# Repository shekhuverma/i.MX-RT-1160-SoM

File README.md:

You can read the full blog post [here](https://shekharverma.com/posts/imxrt_som/)!

**The SoM Features**
* i.MX RT 1160 MCU (MIMXRT1166DVM6A)
* 128 Mb SD RAM
* 128 Mb QSPI Flash
* 4 Gb eMMC
* 10/100 Mbps RMII Ethernet PHY
* 2 Lane MIPI-DSI
* 2 Lane MIPI-CSI
* 2 X USB 2.0
* 2 X I2C
* UART to USB Convertor
* Multiple GPIOs
* 2 X 48 Pin Board-to-Board Connector

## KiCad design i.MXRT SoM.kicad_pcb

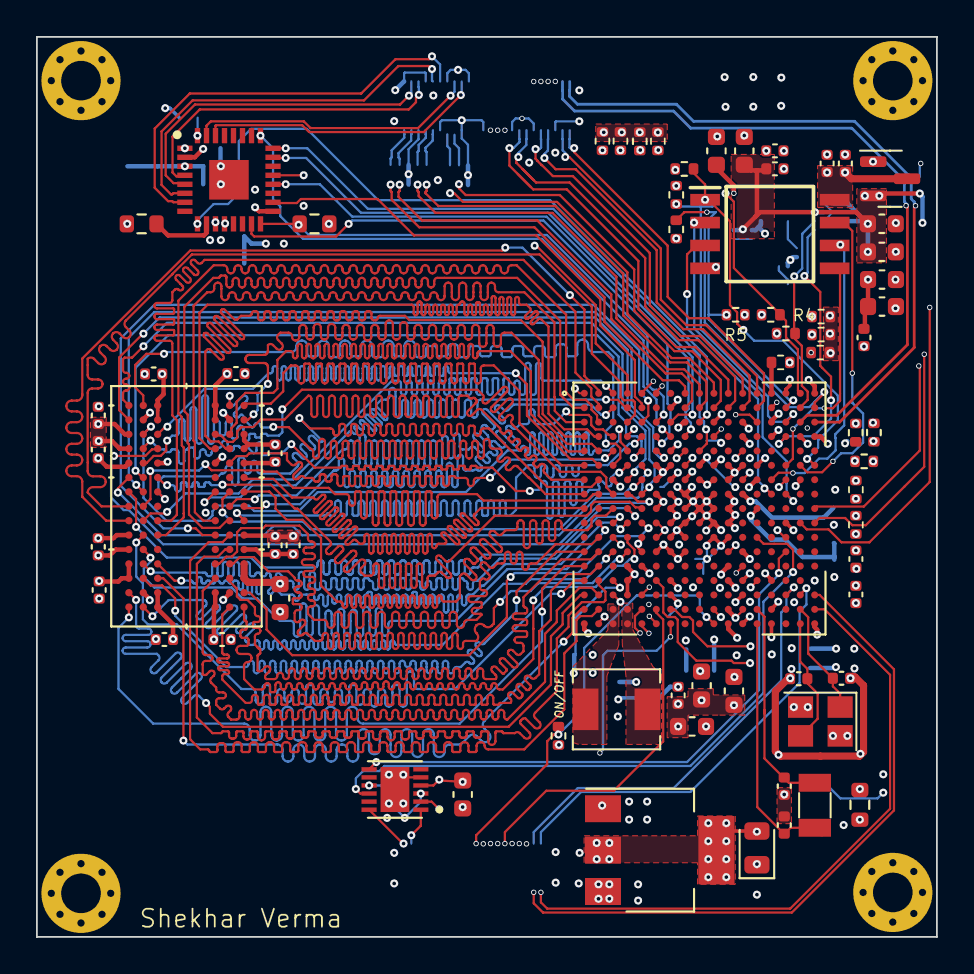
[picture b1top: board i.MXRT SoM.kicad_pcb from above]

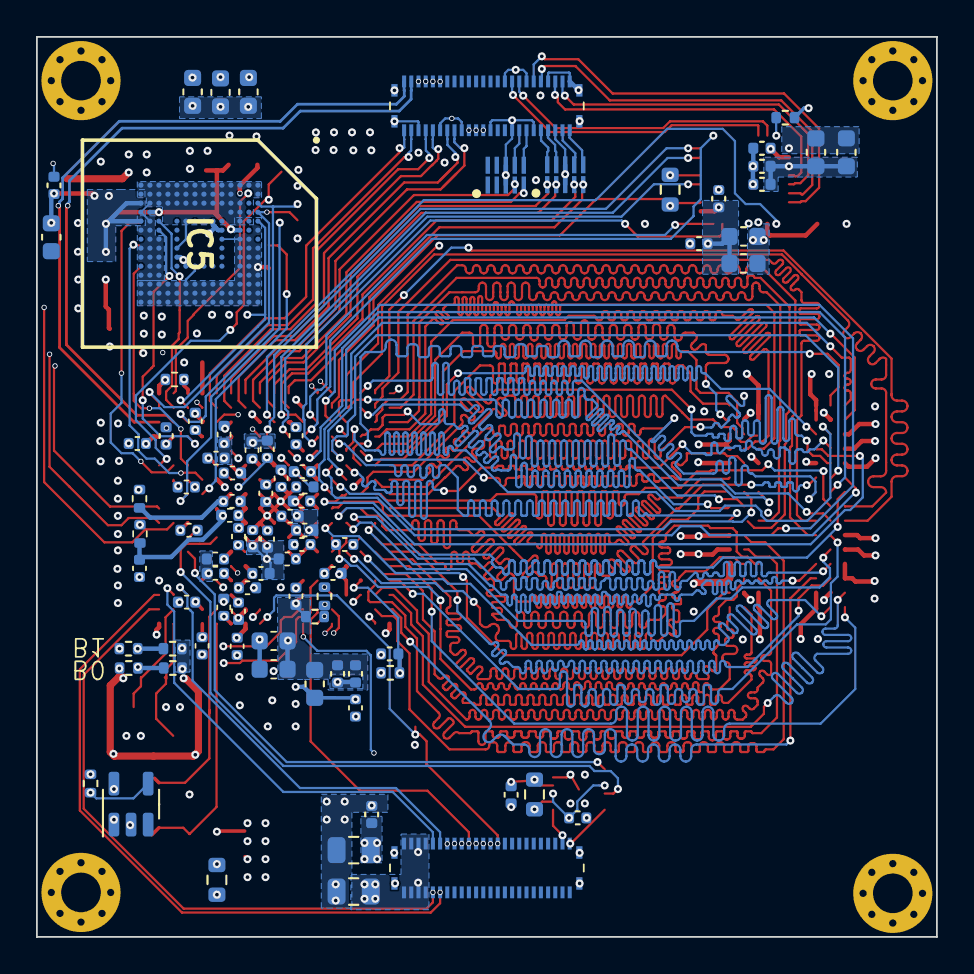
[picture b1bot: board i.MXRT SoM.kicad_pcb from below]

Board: 6 copper layers, 50.0 x 50.0 mm, 157 parts (85 on the bottom side), 170 nets.

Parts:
C1, C43, C49, C50, C58: 22uF; C_0603_1608Metric
C2, C8, C9, C10, C11, C21, C31, C35, C45, C57: 4.7uF; C_0402_1005Metric
C3, C15, C16, C26, C37, C41, C46, C48, C51, C53, C59, C60, C61, C62, C63, C64, C65, C66, C67, C68, C76, C89, C96: 0.1uF; C_0402_1005Metric
C4, C5, C6, C14, C20, C25, C28, C32, C36, C55: 1uF; C_0402_1005Metric
C7, C17: 0.22uF; C_0402_1005Metric
C12, C13, C18, C19, C22, C23, C24, C27, C29, C30, C33, C34, C40, C44, C69, C92, C99: 2.2uF; C_0402_1005Metric
C38, C39, C87, C88: 4.7pF; C_0402_1005Metric
C42, C47, C78, C82: 10uF; C_0603_1608Metric
C52, C72, C80, C83, C85: 100nF; C_0402_1005Metric
C54, C73, C81, C86, C98: 1uF; C_0603_1608Metric
C56: 2nF; C_0402_1005Metric
C70, C71: 10uF; C_0805_2012Metric
C74, C75: 2.2uF; C_0603_1608Metric
C77, C79: 10nF; C_0402_1005Metric
C84: 4.7uF; C_0603_1608Metric
C90, C91, C93, C94, C95: 0.1uF; C_0603_1608Metric
D1: Green LED; LED_0805_2012Metric
FB1, FB2, FB3, FB4: 120Ohm@100Mhz; R_0402_1005Metric
H1, H2, H3, H4: MountingHole_Pad; MountingHole_2.2mm_M2_Pad_Via
IC1, IC2: ECMF04-4HSM10
IC3: DP83826ERHBR; QFN50P500X500X100-33N-D
IC5: THGBMTG5D1LBAIL; BGA153C50P14X14_1150X1300X80
IC6: W25Q16JVSSIQ; SOIC127P790X216-8N
J1, J2: DF40GB-48DP-0.4V_58_; DF40GB48DP04V58
L1: 4.7uH; AMDLA4020Q-4R7MT
R1: 30K; R_0402_1005Metric
R2, R3, R4, R5, R7, R8, R32: 10K; R_0402_1005Metric
R6, R11: 4.7K; R_0402_1005Metric
R9, R12, R25, R26: DNP; R_0402_1005Metric
R10, R13, R14, R15, R16, R17, R18, R19, R20, R21, R22, R23, R24: 100K; R_0402_1005Metric
R27: 100; R_0603_1608Metric
R28, R41: 10K; R_0603_1608Metric
R29: 6.49K 1%; R_0603_1608Metric
R30, R31: 2.49K 1%; R_0603_1608Metric
R36: 0; R_0402_1005Metric
U1: MIMXRT1166DVM6A
U3: AS4C4M32S-6BIN
U4: LD1117S33TR_SOT223; SOT-223-3_TabPin2
U5: RP300N27AA; SOT-23-5
U6: FT234XD-R; SON45P300X300X80-13N
U7: MCP1700T-1802E/TT; SOT-23
Y1: Crystal_GND24; Crystal_SMD_SeikoEpson_FA238-4Pin_3.2x2.5mm
Y3: 32.768Khz; Crystal_SMD_3215-2Pin_3.2x1.5mm

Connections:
5V: C70.1, J2.21, J2.22, J2.23, J2.24, J2.45, J2.46, J2.47, J2.48, U4.3 (VI)
/MCU_POWER/VDD_SNVS_DIG: C17.1, U1.T14 (VDD_SNVS_DIG)
A0: U1.A3 (GPIO_EMC_B1_09), U3.G8 (A0)
A1: U1.A2 (GPIO_EMC_B1_10), U3.G9 (A1)
A2: U1.C2 (GPIO_EMC_B1_11), U3.F7 (A2)
A3: U1.C5 (GPIO_EMC_B1_12), U3.F3 (A3)
A4: U1.D5 (GPIO_EMC_B1_13), U3.G1 (A4)
A5: U1.B1 (GPIO_EMC_B1_14), U3.G2 (A5)
A6: U1.C1 (GPIO_EMC_B1_15), U3.G3 (A6)
A7: U1.D3 (GPIO_EMC_B1_16), U3.H1 (A7)
A8: U1.B3 (GPIO_EMC_B1_17), U3.H2 (A8)
A9: U1.B4 (GPIO_EMC_B1_18), U3.J3 (A9)
A10: U1.B2 (GPIO_EMC_B1_23), U3.G7 (A10)
A11: U1.C4 (GPIO_EMC_B1_19), U3.H9 (A11)
BA0: U1.G2 (GPIO_EMC_B1_21), U3.J7 (BA0)
BA1: U1.H2 (GPIO_EMC_B1_22), U3.H8 (BA1)
CSI_CK_N: J1.5, U1.A12 (MIPI_CSI_CKN)
CSI_CK_P: J1.4, U1.B12 (MIPI_CSI_CKP)
CSI_D0_N: J1.8, U1.A11 (MIPI_CSI_DN0)
CSI_D0_P: J1.7, U1.B11 (MIPI_CSI_DP0)
CSI_D1_N: J1.2, U1.A13 (MIPI_CSI_DN1)
CSI_D1_P: J1.1, U1.B13 (MIPI_CSI_DP1)
DCDC_1V8: C20.1, C26.1, C33.1, C37.1, C40.1, C42.1, C43.1, C46.1, FB1.2, FB3.2, U1.G16 (ADC_VREFH), U1.K15 (VDDA_ADC_1P8), U1.M6 (DCDC_ANA_SENSE), U1.M7 (DCDC_ANA), U1.M8 (DCDC_ANA), U1.M11 (VDDA_1P8_IN)
DCDC_IN: C4.1, C10.1, C11.1, C12.1, C13.1, C18.1, C21.1, C22.1, C23.1, C24.1, C27.1, C30.1, C31.1, C45.1, C48.1, C50.1, C52.1, C53.1, C54.1, C55.1, C57.1, C58.1, C59.1, C60.1, C61.1, C62.1, C63.1, C64.1, C65.1, C66.1, C67.1, C68.1, C71.1, C72.1, C74.1, C75.1, C76.2, C77.1, C78.1, C79.2, C80.2, C81.2, C82.2, C83.1, C84.1, C86.2, C89.2, C90.2, C91.2, D1.2 (A), FB2.2, FB4.2, IC3.3 (VDDA3V3), IC3.17 (VDDIO), IC5.E6 (VCC_1), IC5.F5 (VCC_2), IC5.J10 (VCC_3), IC5.K9 (VCC_4), IC6.8 (VCC), R1.2, R2.2, R3.2, R4.2, R5.2, R7.2, R8.2, R9.2, R11.2, R26.1, R28.1, R31.1, R32.1, R41.2, U1.D12 (NVCC_DISP1), U1.D14 (NVCC_SD1), U1.E7 (NVCC_DISP2), U1.F6 (NVCC_EMC1), U1.F7 (NVCC_EMC1), U1.G6 (NVCC_EMC1), U1.G13 (NVCC_SD2), U1.H6 (NVCC_EMC2), U1.J6 (NVCC_EMC2), U1.L5 (DCDC_IN_Q), U1.M5 (DCDC_IN), U1.M12 (NVCC_GPIO), U1.N5 (DCDC_IN), U1.P7 (NVCC_LPSR), U1.R12 (VDD_LPSR_IN), U1.U12 (VDD_SNVS_IN), U3.A7 (VDD), U3.B2 (VDDQ), U3.B7 (VDDQ), U3.C9 (VDDQ), U3.D9 (VDDQ), U3.E1 (VDDQ), U3.F9 (VDD), U3.L1 (VDDQ), U3.L7 (VDD), U3.M9 (VDDQ), U3.N9 (VDDQ), U3.P2 (VDDQ), U3.P7 (VDDQ), U3.R7 (VDD), U4.2 (VO), U5.5 (VDD), U6.4 (VCC), U7.3 (VI)
DCDC_LN: L1.1, U1.T4 (DCDC_LN), U1.U4 (DCDC_LN)
DCDC_LP: L1.2, U1.T3 (DCDC_LP), U1.U3 (DCDC_LP)
DQ0: U1.F3 (GPIO_EMC_B1_00), U3.R8 (DQ0)
DQ1: U1.F2 (GPIO_EMC_B1_01), U3.N7 (DQ1)
DQ2: U1.G4 (GPIO_EMC_B1_02), U3.R9 (DQ2)
DQ3: U1.E4 (GPIO_EMC_B1_03), U3.N8 (DQ3)
DQ4: U1.H5 (GPIO_EMC_B1_04), U3.P9 (DQ4)
DQ5: U1.F4 (GPIO_EMC_B1_05), U3.M8 (DQ5)
DQ6: U1.H4 (GPIO_EMC_B1_06), U3.M7 (DQ6)
DQ7: U1.H3 (GPIO_EMC_B1_07), U3.L8 (DQ7)
DQ8: U1.E3 (GPIO_EMC_B1_30), U3.L2 (DQ8)
DQ9: U1.D2 (GPIO_EMC_B1_31), U3.M3 (DQ9)
DQ10: U1.D1 (GPIO_EMC_B1_32), U3.M2 (DQ10)
DQ11: U1.E2 (GPIO_EMC_B1_33), U3.P1 (DQ11)
DQ12: U1.E1 (GPIO_EMC_B1_34), U3.N2 (DQ12)
DQ13: U1.F1 (GPIO_EMC_B1_35), U3.R1 (DQ13)
DQ14: U1.G1 (GPIO_EMC_B1_36), U3.N3 (DQ14)
DQ15: U1.H1 (GPIO_EMC_B1_37), U3.R2 (DQ15)
DQ16: U1.K2 (GPIO_EMC_B2_00), U3.E8 (DQ16)
DQ17: U1.K4 (GPIO_EMC_B2_01), U3.D7 (DQ17)
DQ18: U1.K3 (GPIO_EMC_B2_02), U3.D8 (DQ18)
DQ19: U1.R1 (GPIO_EMC_B2_03), U3.B9 (DQ19)
DQ20: U1.M1 (GPIO_EMC_B2_04), U3.C8 (DQ20)
DQ21: U1.N1 (GPIO_EMC_B2_05), U3.A9 (DQ21)
DQ22: U1.T1 (GPIO_EMC_B2_06), U3.C7 (DQ22)
DQ23: U1.M3 (GPIO_EMC_B2_07), U3.A8 (DQ23)
DQ24: U1.N2 (GPIO_EMC_B2_09), U3.A2 (DQ24)
DQ25: U1.R2 (GPIO_EMC_B2_10), U3.C3 (DQ25)
DQ26: U1.L4 (GPIO_EMC_B2_11), U3.A1 (DQ26)
DQ27: U1.M2 (GPIO_EMC_B2_12), U3.C2 (DQ27)
DQ28: U1.K5 (GPIO_EMC_B2_13), U3.B1 (DQ28)
DQ29: U1.M4 (GPIO_EMC_B2_14), U3.D2 (DQ29)
DQ30: U1.L2 (GPIO_EMC_B2_15), U3.D3 (DQ30)
DQ31: U1.P2 (GPIO_EMC_B2_16), U3.E2 (DQ31)
DQM0: U1.F5 (GPIO_EMC_B1_08), U3.K9 (DQM0)
DQM1: U1.J1 (GPIO_EMC_B1_38), U3.K1 (DQM1)
DQM2: U1.P1 (GPIO_EMC_B2_08), U3.F8 (DQM2)
DQM3: U1.T2 (GPIO_EMC_B2_17), U3.F2 (DQM3)
DSI_CK_MCU_N: IC1.2 (D1-_1), U1.A9 (MIPI_DSI_CKN)
DSI_CK_MCU_P: IC1.1 (D1+_1), U1.B9 (MIPI_DSI_CKP)
DSI_CK_N: IC1.9 (D1-_2), J1.21
DSI_CK_P: IC1.10 (D1+_2), J1.20
DSI_D0_MCU_N: IC1.5 (D2-_1), U1.A8 (MIPI_DSI_DN0)
DSI_D0_MCU_P: IC1.4 (D2+_1), U1.B8 (MIPI_DSI_DP0)
DSI_D0_N: IC1.6 (D2-_2), J1.24
DSI_D0_P: IC1.7 (D2+_2), J1.23
DSI_D1_MCU_N: IC2.5 (D2-_1), U1.A10 (MIPI_DSI_DN1)
DSI_D1_MCU_P: IC2.4 (D2+_1), U1.B10 (MIPI_DSI_DP1)
DSI_D1_N: IC2.6 (D2-_2), J1.18
DSI_D1_P: IC2.7 (D2+_2), J1.17
EMMC_CLK: IC5.M6 (CLK), U1.D15 (GPIO_SD_B1_01)
EMMC_CMD: IC5.M5 (CMD), R2.1, U1.B16 (GPIO_SD_B1_00)
EMMC_D0: IC5.A3 (DAT0), R8.1, U1.C15 (GPIO_SD_B1_02)
EMMC_D1: IC5.A4 (DAT1), R7.1, U1.B17 (GPIO_SD_B1_03)
EMMC_D2: IC5.A5 (DAT2), R5.1, U1.B15 (GPIO_SD_B1_04)
EMMC_D3: IC5.B2 (DAT3), R4.1, U1.A16 (GPIO_SD_B1_05)
ENET_CRS_DV: IC3.18 (RX_DV/CRS_DV/STRAP10), U1.B5 (GPIO_DISP_B2_08)
ENET_INT: IC3.21 (PWRDN/INT), R31.2, U1.P17 (GPIO_AD_12)
ENET_LED0: IC3.30 (LED0/STRAP2), J1.40
ENET_LED1: IC3.31 (CLKOUT/LED1/STRAP1), J1.41
ENET_MDC: IC3.12 (MDC), U1.U2 (GPIO_EMC_B2_19)
ENET_MDIO: IC3.11 (MDIO), U1.R3 (GPIO_EMC_B2_20)
ENET_RST: IC3.32 (RST_N), R36.2
ENET_RX_D0: IC3.16 (STRAP0/RX_D0), R30.2, U1.C6 (GPIO_DISP_B2_06)
ENET_RX_D1: IC3.15 (STRAP9/RX_D1), U1.D6 (GPIO_DISP_B2_07)
ENET_RX_ER: IC3.20 (RX_ER/STRAP6), U1.D8 (GPIO_DISP_B2_09)
ENET_TX_CLK: IC3.9 (XI/50MHZIN), R20.2, U1.C9 (GPIO_DISP_B2_05)
ENET_TX_D0: IC3.24 (TX_D0), R23.2, U1.E9 (GPIO_DISP_B2_02)
ENET_TX_D1: IC3.25 (TX_D1), R24.2, U1.D7 (GPIO_DISP_B2_03)
ENET_TX_EN: IC3.23 (TX_EN), R19.2, U1.C7 (GPIO_DISP_B2_04)
GND: C1.2, C2.2, C3.2, C4.2, C5.2, C6.2, C7.2, C8.2, C9.2, C10.2, C11.2, C12.2, C13.2, C14.2, C15.2, C16.2, C17.2, C18.2, C19.2, C20.2, C21.2, C22.2, C23.2, C24.2, C25.2, C26.2, C27.2, C28.2, C29.2, C30.2, C31.2, C32.2, C33.2, C34.1, C35.1, C36.2, C37.2, C38.1, C39.2, C40.2, C41.2, C42.2, C43.2, C44.2, C45.2, C46.2, C47.2, C48.2, C49.2, C50.2, C51.2, C52.2, C53.2, C54.2, C55.2, C56.1, C57.2, C58.2, C59.2, C60.2, C61.2, C62.2, C63.2, C64.2, C65.2, C66.2, C67.2, C68.2, C69.2, C70.2, C71.2, C72.2, C73.2, C74.2, C75.2, C76.1, C77.2, C78.2, C79.1, C80.1, C81.1, C82.1, C83.2, C84.2, C85.2, C86.1, C87.1, C88.2, C89.1, C90.1, C91.1, C92.2, C93.1, C94.1, C95.1, C96.1, C98.1, C99.2, H1.1, H2.1, H3.1, H4.1, IC1.3 (GND_1), IC1.8 (GND_2), IC2.3 (GND_1), IC2.8 (GND_2), IC3.1 (MODESELECT), IC3.33 (EP), IC5.A1 (NC), IC5.A2 (NC), IC5.A6 (VSS_1), IC5.A8 (NC), IC5.A9 (NC), IC5.A10 (NC), IC5.A11 (NC), IC5.A12 (NC), IC5.A13 (NC), IC5.A14 (NC), IC5.B1 (NC), IC5.B7 (NC), IC5.B8 (NC), IC5.B9 (NC), IC5.B10 (NC), IC5.B11 (NC), IC5.B12 (NC), IC5.B13 (NC), IC5.B14 (NC), IC5.C1 (NC), IC5.C3 (NC), IC5.C4 (VSSQ_1), IC5.C5 (NC), IC5.C7 (NC), IC5.C8 (NC), IC5.C9 (NC), IC5.C10 (NC), IC5.C11 (NC), IC5.C12 (NC), IC5.C13 (NC), IC5.C14 (NC), IC5.D1 (NC), IC5.D2 (NC), IC5.D3 (NC), IC5.D4 (NC), IC5.D12 (NC), IC5.D13 (NC), IC5.D14 (NC), IC5.E1 (NC), IC5.E2 (NC), IC5.E3 (NC), IC5.E7 (VSS_2), IC5.E12 (NC), IC5.E13 (NC), IC5.E14 (NC), IC5.F1 (NC), IC5.F2 (NC), IC5.F3 (NC), IC5.F12 (NC), IC5.F13 (NC), IC5.F14 (NC), IC5.G1 (NC), IC5.G2 (NC), IC5.G3 (NC), IC5.G5 (VSS_3), IC5.G12 (NC), IC5.G13 (NC), IC5.G14 (NC), IC5.H1 (NC), IC5.H2 (NC), IC5.H3 (NC), IC5.H10 (VSS_4), IC5.H12 (NC), IC5.H13 (NC), IC5.H14 (NC), IC5.J1 (NC), IC5.J2 (NC), IC5.J3 (NC), IC5.J5 (VSS_5), IC5.J12 (NC), IC5.J13 (NC), IC5.J14 (NC), IC5.K1 (NC), IC5.K2 (NC), IC5.K3 (NC), IC5.K8 (VSS_6), IC5.K12 (NC), IC5.K13 (NC), IC5.K14 (NC), IC5.L1 (NC), IC5.L2 (NC), IC5.L3 (NC), IC5.L12 (NC), IC5.L13 (NC), IC5.L14 (NC), IC5.M1 (NC), IC5.M2 (NC), IC5.M3 (NC), IC5.M7 (NC), IC5.M8 (NC), IC5.M9 (NC), IC5.M10 (NC), IC5.M11 (NC), IC5.M12 (NC), IC5.M13 (NC), IC5.M14 (NC), IC5.N1 (NC), IC5.N2 (VSSQ_2), IC5.N3 (NC), IC5.N5 (VSSQ_3), IC5.N6 (NC), IC5.N7 (NC), IC5.N8 (NC), IC5.N9 (NC), IC5.N10 (NC), IC5.N11 (NC), IC5.N12 (NC), IC5.N13 (NC), IC5.N14 (NC), IC5.P1 (NC), IC5.P2 (NC), IC5.P4 (VSSQ_4), IC5.P6 (VSSQ_5), IC5.P8 (NC), IC5.P9 (NC), IC5.P11 (NC), IC5.P12 (NC), IC5.P13 (NC), IC5.P14 (NC), IC6.4 (GND), J1.3, J1.6, J1.9, J1.13, J1.16, J1.19, J1.22, J1.30, J1.39, J1.42, J1.45, J1.48, J1.MP1, J1.MP2, J1.MP3, J1.MP4, J2.12, J2.18, J2.MP1, J2.MP2, J2.MP3, J2.MP4, R6.1, R10.1, R12.1, R13.1, R14.1, R15.1, R16.1, R17.1, R18.1, R19.1, R20.1, R21.1, R22.1, R23.1, R24.1, R27.2, R29.1, R30.1, U1.A1 (VSS), U1.A17 (VSS), U1.B7 (VSS), U1.C8 (VSS), U1.C10 (VSS), U1.C12 (VSS), U1.C14 (VSS), U1.D4 (VSS), U1.F11 (VSS), U1.F12 (VSS), U1.F13 (VSS), U1.G3 (VSS), U1.G7 (VSS), U1.G8 (VSS), U1.G9 (VSS), U1.G10 (VSS), U1.G11 (VSS), U1.G15 (VSS), U1.H7 (VSS), U1.H11 (VSS), U1.J7 (VSS), U1.J11 (VSS), U1.K6 (DCDC_GND), U1.K7 (DCDC_GND), U1.K11 (VSS), U1.L3 (VSS), U1.L6 (DCDC_GND), U1.L10 (VSS), U1.L11 (VSS), U1.L15 (VSS), U1.N4 (DCDC_MODE), U1.P4 (VSS), U1.P14 (VSS), U1.R4 (VSS), U1.R7 (VSS), U1.T11 (TEST_MODE), U1.T12 (VSS), U1.U1 (VSS), U1.U17 (VSS), U3.A3 (VSS), U3.B3 (VSSQ), U3.B8 (VSSQ), U3.C1 (VSSQ), U3.D1 (VSSQ), U3.E9 (VSSQ), U3.F1 (VSS), U3.L3 (VSS), U3.L9 (VSSQ), U3.M1 (VSSQ), U3.N1 (VSSQ), U3.P3 (VSSQ), U3.P8 (VSSQ), U3.R3 (VSS), U4.1 (GND), U5.2 (GND), U6.5 (GND), U6.13 (GND), U7.1 (GND), Y1.2, Y1.4
GPIO1: J1.12, U1.A4 (GPIO_DISP_B2_15)
GPIO2: J1.10, U1.A6 (GPIO_DISP_B2_11)
GPIO3: J1.11, U1.A5 (GPIO_DISP_B2_13)
GPIO4: J2.17, U1.P13 (GPIO_AD_05)
GPIO5: J2.44, U1.T17 (GPIO_AD_07)
GPIO6: J2.43, U1.R17 (GPIO_AD_10)
GPIO_LPSR_02: R9.1, R10.2, U1.P6 (GPIO_LPSR_02)
GPIO_LPSR_03: R11.1, R12.2, U1.T7 (GPIO_LPSR_03)
I2C2_SCL: J2.19, U1.R15 (GPIO_AD_08)
I2C2_SDA: J2.20, U1.R16 (GPIO_AD_09)
JTAG_TCK/SWCLK: J2.15, U1.T6 (GPIO_LPSR_14)
JTAG_TDI: J2.14, U1.U5 (GPIO_LPSR_12)
JTAG_TDO: J2.13, U1.T5 (GPIO_LPSR_11)
JTAG_TMS/SWDIO: J2.16, U1.U7 (GPIO_LPSR_15)
NRST: R28.2, U5.1 (~MR)
unnamed: D1.1 (K), R27.1
unnamed: C56.2, IC3.2 (CEXT)
unnamed: IC3.10 (RBIAS), R29.2
unnamed: C73.1, IC5.C2 (VDDI)
unnamed: C7.1, R1.1, U1.P3 (DCDC_PSWITCH)
unnamed: C14.1, C16.1, FB4.1, U1.J13 (VDDA_ADC_3P3)
unnamed: C35.2, U1.P12 (VDD_LPSR_ANA)
unnamed: C34.2, U1.P11 (VDD_LPSR_DIG)
unnamed: C25.1, FB1.1, U1.F9 (VDD_MIPI_1P8)
unnamed: C36.1, FB3.1, U1.H12 (VDD_USB_1P8)
unnamed: C32.1, FB2.1, U1.G12 (VDD_USB_3P3)
unnamed: R17.2, U1.D10 (GPIO_DISP_B1_06)
unnamed: R18.2, U1.E12 (GPIO_DISP_B1_07)
unnamed: R13.2, U1.A15 (GPIO_DISP_B1_08)
unnamed: R14.2, U1.C13 (GPIO_DISP_B1_09)
unnamed: R15.2, U1.B14 (GPIO_DISP_B1_10)
unnamed: R16.2, U1.A14 (GPIO_DISP_B1_11)
unnamed: R21.2, U1.E8 (GPIO_DISP_B2_00)
unnamed: R22.2, U1.F8 (GPIO_DISP_B2_01)
unnamed: R32.2, U1.R5 (GPIO_LPSR_10)
unnamed: R6.2, U1.U6 (GPIO_LPSR_13)
unnamed: C39.1, U1.U16 (XTALI), Y1.3
unnamed: C38.2, U1.T16 (XTALO), Y1.1
unnamed: C85.1, U6.3 (3V3OUT), U6.9 (VCCIO)
unnamed: R41.1, U6.2 (~RESET#)
ON/OFF: J2.11, R26.2, U1.U10 (ONOFF)
POR_B: R25.2, R36.1, U1.T10 (POR_B), U5.4 (out)
QSPI_CLK: IC6.6 (CLK), U1.G14 (GPIO_SD_B2_07)
QSPI_CS: IC6.1 (/CS), R3.1, U1.F17 (GPIO_SD_B2_06)
QSPI_IO_0: IC6.5 (DI_(IO0)), U1.F15 (GPIO_SD_B2_08)
QSPI_IO_1: IC6.2 (DO_(IO1)), U1.H15 (GPIO_SD_B2_09)
QSPI_IO_2: IC6.3 (IO2), U1.H14 (GPIO_SD_B2_10)
QSPI_IO_3: IC6.7 (IO3), U1.F16 (GPIO_SD_B2_11)
RD_N: IC3.4 (RD_M), J1.46
RD_P: IC3.5 (RD_P), J1.47
RTC_XTALI: C88.1, U1.T13 (RTC_XTALI), Y3.2
RTC_XTALO: C87.2, U1.U13 (RTC_XTALO), Y3.1
SDCAS: U1.J5 (GPIO_EMC_B1_24), U3.K7 (*CAS)
SDCKE: U1.G5 (GPIO_EMC_B1_27), U3.J2 (CKE)
SDCLK: U1.J3 (GPIO_EMC_B1_26), U3.J1 (CLK)
SDCS: U1.E6 (GPIO_EMC_B1_29), U3.J8 (*CS)
SDRAS: U1.J4 (GPIO_EMC_B1_25), U3.J9 (*RAS)
SDWE: U1.E5 (GPIO_EMC_B1_28), U3.K8 (*WE)
TD_N: IC3.6 (TD_M), J1.44
TD_P: IC3.7 (TD_P), J1.43
UART_RX: U1.M15 (GPIO_AD_25), U6.7 (TXD)
UART_TX: U1.L13 (GPIO_AD_24), U6.10 (RXD)
UART_USB_N: J2.2, U6.1 (USBDM)
UART_USB_P: J2.1, U6.12 (USBDP)
USB2_DN: J1.26, U1.C16 (USB2_DN)
USB2_DP: J1.25, U1.C17 (USB2_DP)
USB_OTG1: C99.1, U1.D16 (USB2_VBUS)
USB_OTG2: C69.1, U1.D17 (USB1_VBUS)
USB_OTG2_ID: J1.29, U1.K16 (GPIO_AD_32)
USB_OTG2_OC: J1.28, U1.K17 (GPIO_AD_30)
USB_OTG2_PWR: J1.27, U1.J17 (GPIO_AD_31)
VDD_1P0: C28.1, C29.1, U1.F10 (VDD_MIPI_1P0), U1.N11 (VDDA_1P0)
VDD_1V8: C92.1, C93.2, C94.2, C95.2, C96.2, C98.2, IC5.C6 (VCCQ_1), IC5.M4 (VCCQ_2), IC5.N4 (VCCQ_3), IC5.P3 (VCCQ_4), IC5.P5 (VCCQ_5), U7.2 (VO)
VDD_SNVS_ANA: C15.1, C19.1, R25.1, U1.U11 (NVCC_SNVS), U1.U14 (VDD_SNVS_ANA)
VDD_SOC: C1.1, C2.1, C3.1, C5.1, C6.1, C8.1, C9.1, C41.1, C44.1, C47.1, C49.1, C51.1, U1.H8 (VDD_SOC_IN), U1.H9 (VDD_SOC_IN), U1.H10 (VDD_SOC_IN), U1.J8 (VDD_SOC_IN), U1.J9 (VDD_SOC_IN), U1.J10 (VDD_SOC_IN), U1.K8 (DCDC_DIG), U1.K9 (DCDC_DIG), U1.K10 (VDD_SOC_IN), U1.L7 (DCDC_DIG_SENSE), U1.L8 (DCDC_DIG)

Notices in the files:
parts and their libraries:
Copyright 2021 Accelerated Designs. All rights reserved.
